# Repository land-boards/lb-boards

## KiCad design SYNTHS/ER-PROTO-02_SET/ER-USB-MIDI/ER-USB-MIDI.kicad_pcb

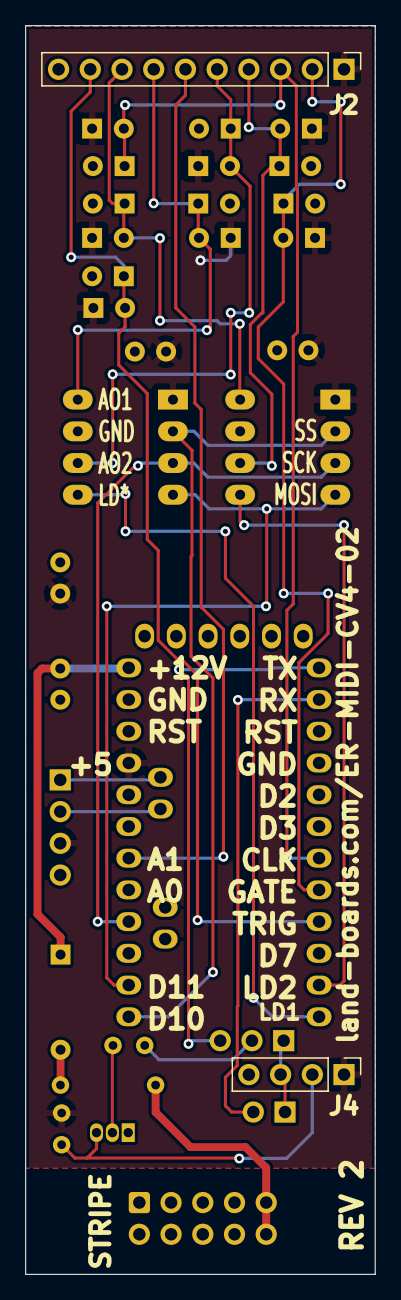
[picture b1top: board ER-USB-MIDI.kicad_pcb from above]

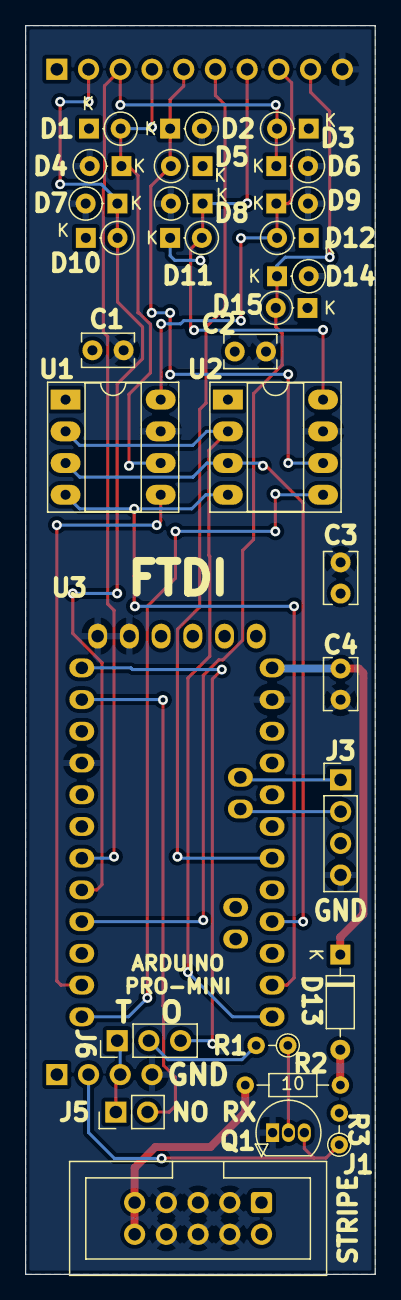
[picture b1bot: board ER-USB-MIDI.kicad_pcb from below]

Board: 2 copper layers, 28.0 x 100.0 mm, 32 parts (30 on the bottom side), 26 nets.

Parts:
C1, C2, C3, C4: 0.1uF; C_Rect_L4.0mm_W2.5mm_P2.50mm
D1, D2, D3, D4, D5, D6, D7, D8, D9, D10, D11, D12, D14, D15: BAT41; D_DO-35_SOD27_P2.54mm_Vertical_KathodeUp
D13: BAT41; D_DO-35_SOD27_P7.62mm_Horizontal
J1: CONN, IDC, 2X5; IDC-Header_2x05_P2.54mm_Vertical
J2: HEADER, STRT, 1x10; PinHeader_1x10_P2.54mm_Vertical
J3: Conn_01x04; PinHeader_1x04_P2.54mm_Vertical
J4: HEADER, STRT, 1x4; PinHeader_1x04_P2.54mm_Vertical
J5: HEADER, STRT, 1x2; PinHeader_1x02_P2.54mm_Vertical
J6: Conn_01x03; PinHeader_1x03_P2.54mm_Vertical
Q1: 2N3904; TO-92_Inline
R1: 2.2K; R_Axial_DIN0204_L3.6mm_D1.6mm_P2.54mm_Vertical
R2: 10; R_Axial_DIN0204_L3.6mm_D1.6mm_P7.62mm_Horizontal
R3: 470; R_Axial_DIN0204_L3.6mm_D1.6mm_P2.54mm_Vertical
U1, U2: MCP4822-E/P; DIP-8_W7.62mm_Socket_LongPads
U3: ARDUINO PRO MINI 5V; ArduProMini

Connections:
+5V: C1.1, C2.1, C3.1, D1.1 (K), D3.1 (K), D5.1 (K), D10.1 (K), D11.1 (K), D12.1 (K), D15.1 (K), J2.1, J3.3, J4.1, R3.2, U1.1 (Vdd), U2.1 (Vdd), U3.22 (Vcc2)
+12P: C4.1, D13.1 (K), U3.19 (RAW)
+12V: J1.9, J1.10, R2.1
/CLK_D: D3.2 (A), D6.1 (K), J2.3, U3.13 (D4)
/CV1_D: D8.1 (K), D11.2 (A), J2.7, U2.8 (VA)
/CV2_D: D2.1 (K), D5.2 (A), J2.5, U2.6 (VB)
/CV3_D: D9.1 (K), D12.2 (A), J2.8, U1.8 (VA)
/CV4_D: D1.2 (A), D4.1 (K), J2.4, U1.6 (VB)
/GATE_D: D7.1 (K), D10.2 (A), J2.2, U3.14 (D5)
/LDAC1*: U2.5 (~LDAC), U3.18 (D9)
/LDAC2*: U1.5 (~LDAC), U3.17 (D8)
/MIDI_IN: J4.3, J5.1, J6.1
/MIDI_OUT: J4.2, Q1.3 (C), R3.1
/MOSI: U1.4 (SDI), U2.4 (SDI), U3.29 (D11)
/POT: J2.6, U3.25 (A1)
/RBO: Q1.2 (B), R1.1
/SCK: U1.3 (SCK), U2.3 (SCK), U3.27 (D13)
/SCL: J3.1, U3.31 (A5/SCL)
/SDA: J3.2, U3.32 (A4/SDA)
/SS: U1.2 (~CS), U2.2 (~CS), U3.30 (D10)
/TRIG_D: D14.1 (K), D15.2 (A), J2.9, U3.15 (D6)
/TXD: J6.3, U3.7 (TX0)
GND: C1.2, C2.2, C3.2, C4.2, D2.2 (A), D4.2 (A), D6.2 (A), D7.2 (A), D8.2 (A), D9.2 (A), D14.2 (A), J1.3, J1.4, J1.5, J1.6, J1.7, J1.8, J2.10, J3.4, J4.4, Q1.1 (E), U1.7 (Vss), U2.7 (Vss), U3.1 (GND), U3.2 (GND2), U3.10 (GND), U3.20 (GND3)
unnamed: D13.2 (A), R2.2
unnamed: J5.2, U3.8 (RX1)
unnamed: J6.2, R1.2

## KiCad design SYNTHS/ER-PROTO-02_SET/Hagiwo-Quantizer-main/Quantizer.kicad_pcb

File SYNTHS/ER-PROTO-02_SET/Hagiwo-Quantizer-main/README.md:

# Hagiwo-Quantizer
A MCP4821 version of Hagiwo Quantizer

This is a version of Hagiwo Quantizer with a MCP4821 12 bit DAC. The code is still under review. Using the new DAC I have to check calibration.

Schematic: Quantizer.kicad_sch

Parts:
C1: 220p; C_Disc_D3.8mm_W2.6mm_P2.50mm
C2, C3: 10nf; C_Disc_D3.8mm_W2.6mm_P2.50mm
C4: 0.1uf; C_Disc_D3.8mm_W2.6mm_P2.50mm
C5: 10uf; CP_Radial_D6.3mm_P2.50mm
C6: 3.3uf; CP_Radial_D6.3mm_P2.50mm
C7: 100nf; C_Disc_D3.8mm_W2.6mm_P2.50mm
D1, D2, D3, D4, D5, D6, D8, D9: D; D_DO-34_SOD68_P7.62mm_Horizontal
D7: LED_ARBG; LED_D5.0mm-4_RGB_Wide_Pins
D10: 4841; D_DO-34_SOD68_P7.62mm_Horizontal
J1: CV; Jack_3.5mm_QingPu_WQP-PJ398SM_Vertical_CircularHoles
J2: SlideCV; Jack_3.5mm_QingPu_WQP-PJ398SM_Vertical_CircularHoles
J3: trigger; Jack_3.5mm_QingPu_WQP-PJ398SM_Vertical_CircularHoles
J4: AudioJack2_SwitchT; Jack_3.5mm_QingPu_WQP-PJ398SM_Vertical_CircularHoles
J5: Conn_02x05_Odd_Even; IDC-Header_2x05_P2.54mm_Vertical
R1, R2, R3, R6, R12: 470; R_Axial_DIN0207_L6.3mm_D2.5mm_P7.62mm_Horizontal
R4: 680K; R_Axial_DIN0207_L6.3mm_D2.5mm_P7.62mm_Horizontal
R5: 100k; R_Axial_DIN0207_L6.3mm_D2.5mm_P7.62mm_Horizontal
R7: 220; R_Axial_DIN0207_L6.3mm_D2.5mm_P7.62mm_Horizontal
R8, R9, R10: 330; R_Axial_DIN0207_L6.3mm_D2.5mm_P7.62mm_Horizontal
RV1: R_POT; Potentiometer_Alps_RK09K_Single_Vertical
SW1: Rotary_Encoder; RotaryEncoder_Alps_EC12E_Vertical_H20mm_CircularMountingHol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
SW2: SW_SPDT; PinHeader_1x03_P2.54mm_Vertical
U1: MCP4821; DIP-8_W7.62mm
U2: L7805; TO-220-3_Vertical
XA1: Arduino_Mini_02_Socket; Arduino_Mini_Socket

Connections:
+5V: C7.1, D1.1 (K), D3.1 (K), D5.1 (K), D8.1 (K), R7.1, RV1.1, U2.3 (OUT), XA1.VIN
+12V: D10.2 (A), J5.9, J5.10
CS: U1.2 (~CS), XA1.D10
CV: D1.2 (A), D2.1 (K), R2.1, R4.1, XA1.A0
GND: C1.2, C2.2, C3.2, C4.1, C5.2, C6.2, C7.2, D2.2 (A), D4.2 (A), D6.2 (A), D7.2 (A), D9.2 (A), J1.S, J2.S, J3.S, J4.S, J5.3, J5.4, J5.5, J5.6, J5.7, J5.8, R4.2, R5.2, RV1.3, SW1.C, SW2.2 (B), U1.5 (~LDAC), U1.7 (Vss), U2.2 (GND), XA1.GND2
Led1: R8.2, XA1.D3
Led2: R9.2, XA1.D5
Led3: R10.2, XA1.D4
unnamed: C4.2, R7.2, U1.1 (Vdd), U1.6 (~SHDN)
unnamed: C5.1, C6.1, D10.1 (K), U2.1 (IN)
unnamed: D5.2 (A), D6.1 (K), J3.T, R6.2
unnamed: D7.1 (RK), R8.1
unnamed: D7.3 (GK), R9.1
unnamed: D7.4 (BK), R10.1
unnamed: D8.2 (A), D9.1 (K), J4.T, R12.1
unnamed: J1.T, R2.2
unnamed: J2.T, R3.2
unnamed: J5.1, J5.2
unnamed: R1.2, RV1.2
unnamed: R12.2, U1.8 (Vout)
RotaryB: C2.1, SW1.B, XA1.D12
RotaryC: C3.1, SW1.A, XA1.D9
SCK: U1.3 (SCK), XA1.D13
SDI: U1.4 (SDI), XA1.D11
SW1: SW2.1 (A), XA1.D7
SW2: SW2.3 (C), XA1.D8
SlideCV: D3.2 (A), D4.1 (K), R3.1, R5.1, XA1.D6
SlidePot: C1.1, R1.1, XA1.A1
Trigger: R6.1, XA1.D2

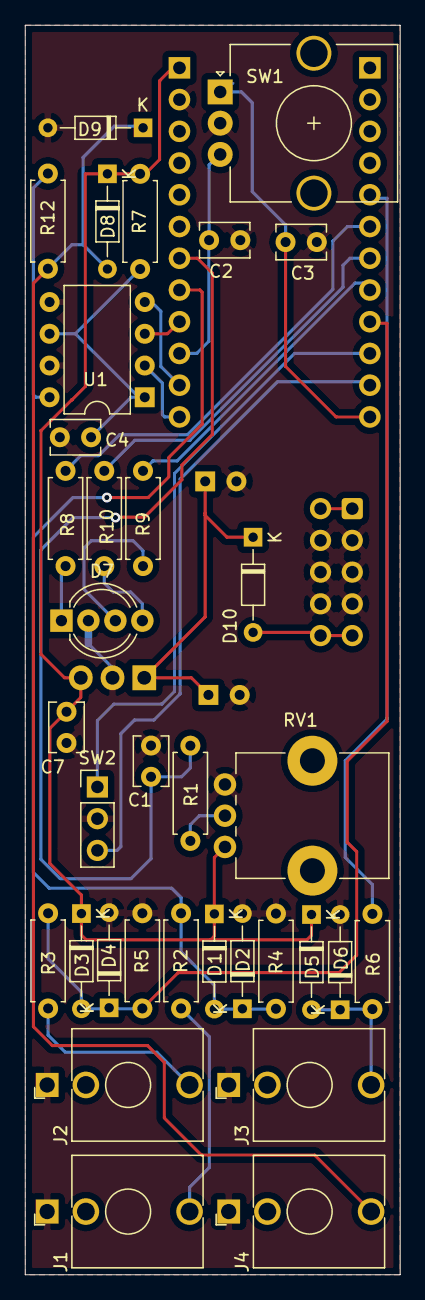
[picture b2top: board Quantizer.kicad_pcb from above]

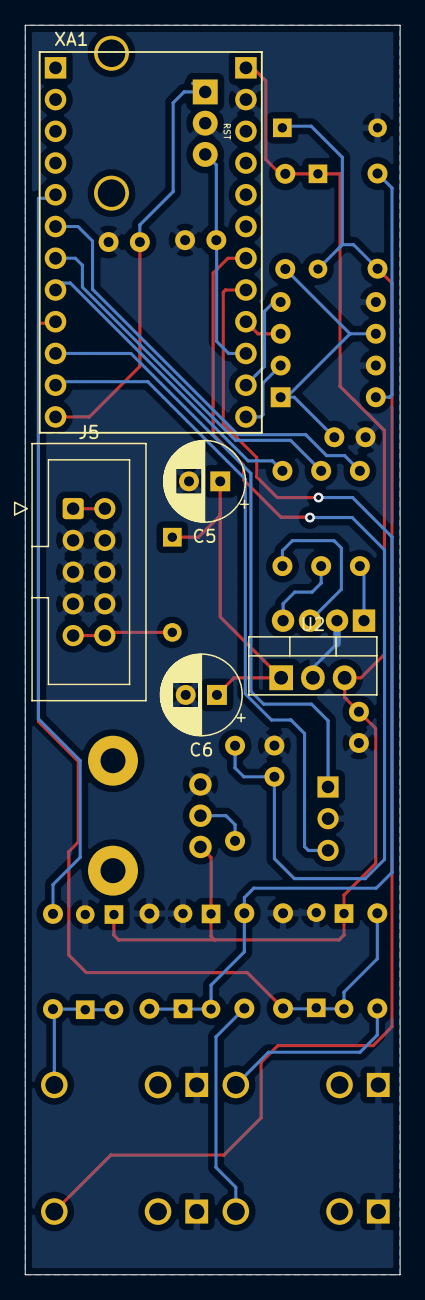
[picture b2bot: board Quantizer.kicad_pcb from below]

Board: 2 copper layers, 30.0 x 100.0 mm, 39 parts (5 on the bottom side), 29 nets.

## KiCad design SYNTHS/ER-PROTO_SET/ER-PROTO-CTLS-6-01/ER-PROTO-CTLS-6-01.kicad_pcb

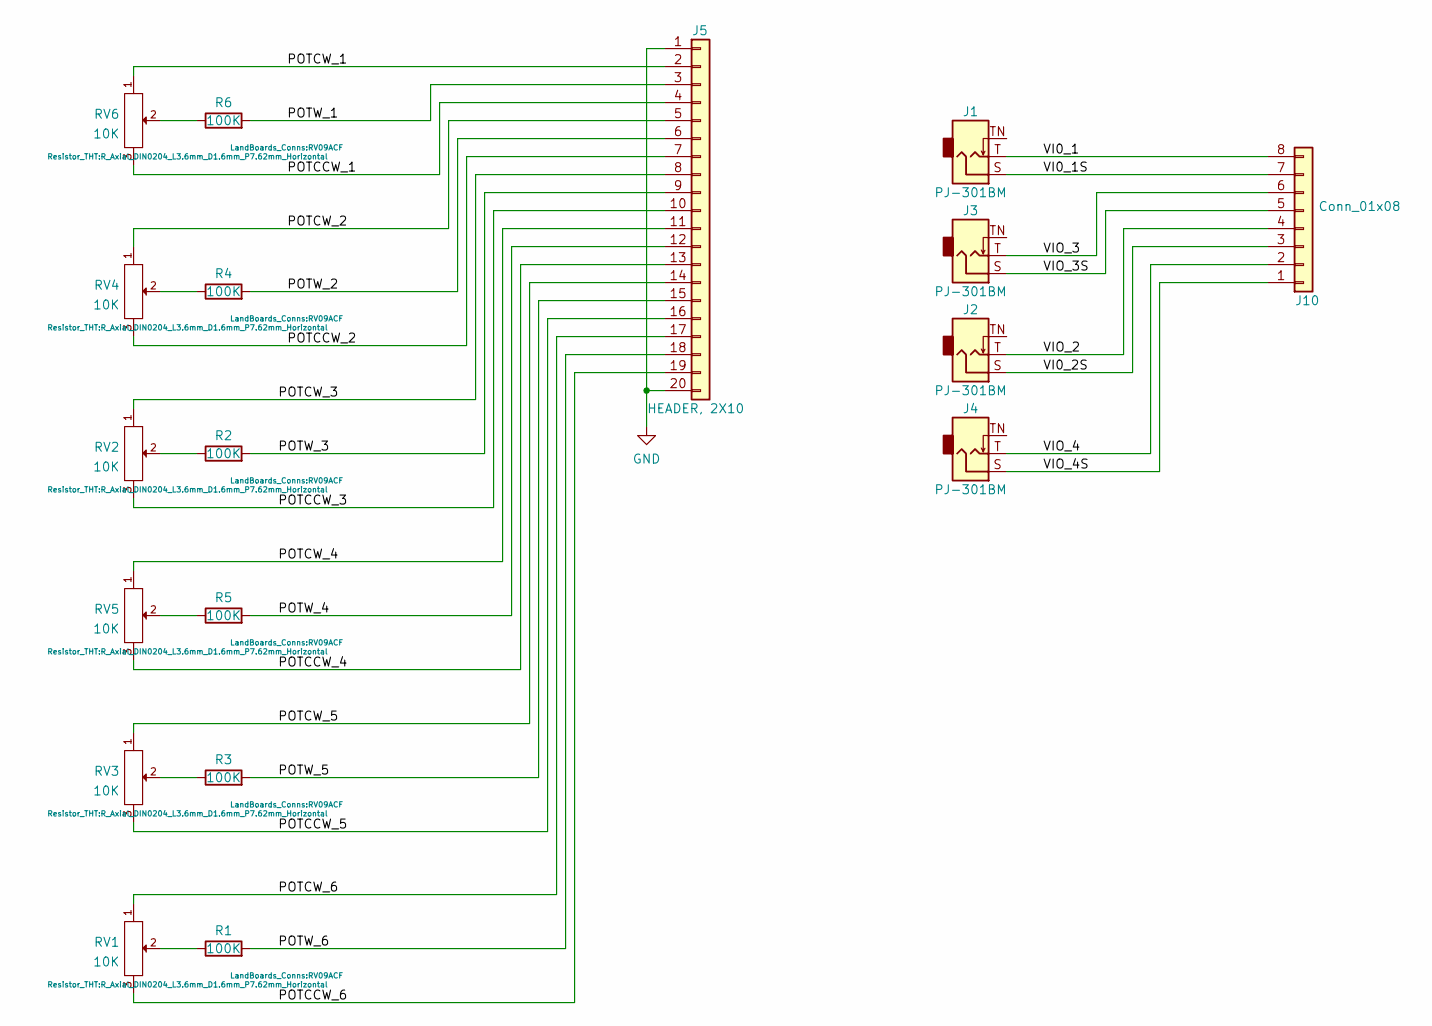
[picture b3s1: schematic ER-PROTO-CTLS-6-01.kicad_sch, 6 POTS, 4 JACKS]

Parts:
J1, J2, J3, J4: PJ-301BM; Jack_3.5mm_QingPu_WQP-PJ301BM_Vertical
J5: HEADER, 2X10; PinHeader_2x10_P2.54mm_Vertical
J10: Conn_01x08; PinHeader_1x08_P2.54mm_Vertical
R1, R2, R3, R4, R5, R6: 100K; R_Axial_DIN0204_L3.6mm_D1.6mm_P7.62mm_Horizontal
RV1, RV2, RV3, RV4, RV5, RV6: 10K; RV09ACF

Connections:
/POTCCW_1: J5.4, RV6.3
/POTCCW_2: J5.7, RV4.3
/POTCCW_3: J5.10, RV2.3
/POTCCW_4: J5.13, RV5.3
/POTCCW_5: J5.16, RV3.3
/POTCCW_6: J5.19, RV1.3
/POTCW_1: J5.2, RV6.1
/POTCW_2: J5.5, RV4.1
/POTCW_3: J5.8, RV2.1
/POTCW_4: J5.11, RV5.1
/POTCW_5: J5.14, RV3.1
/POTCW_6: J5.17, RV1.1
/POTW_1: J5.3, R6.2
/POTW_2: J5.6, R4.2
/POTW_3: J5.9, R2.2
/POTW_4: J5.12, R5.2
/POTW_5: J5.15, R3.2
/POTW_6: J5.18, R1.2
/VI0_1: J1.T, J10.8
/VI0_1S: J1.S, J10.7
/VI0_2S: J2.S, J10.3
/VIO_2: J2.T, J10.4
/VIO_3: J3.T, J10.6
/VIO_3S: J3.S, J10.5
/VIO_4: J4.T, J10.2
/VIO_4S: J4.S, J10.1
GND: J5.1, J5.20
unnamed: R1.1, RV1.2
unnamed: R2.1, RV2.2
unnamed: R3.1, RV3.2
unnamed: R4.1, RV4.2
unnamed: R5.1, RV5.2
unnamed: R6.1, RV6.2

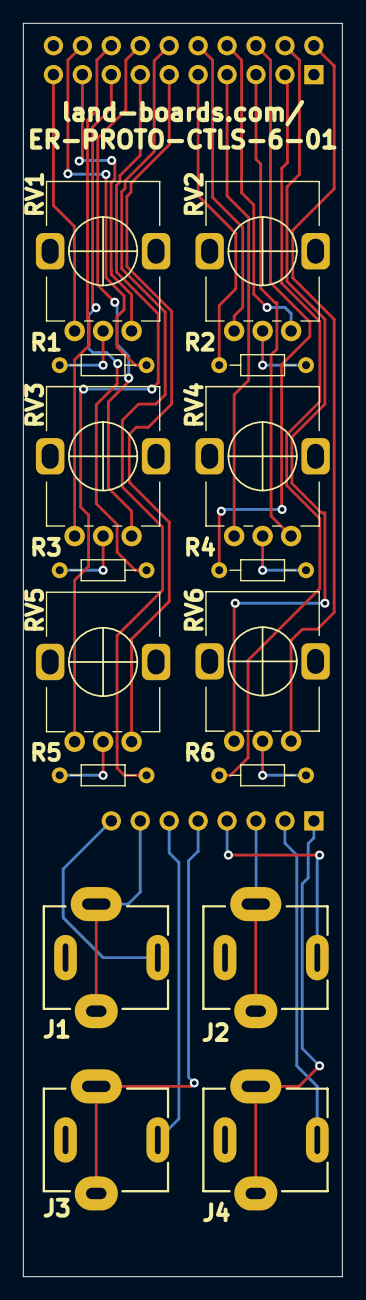
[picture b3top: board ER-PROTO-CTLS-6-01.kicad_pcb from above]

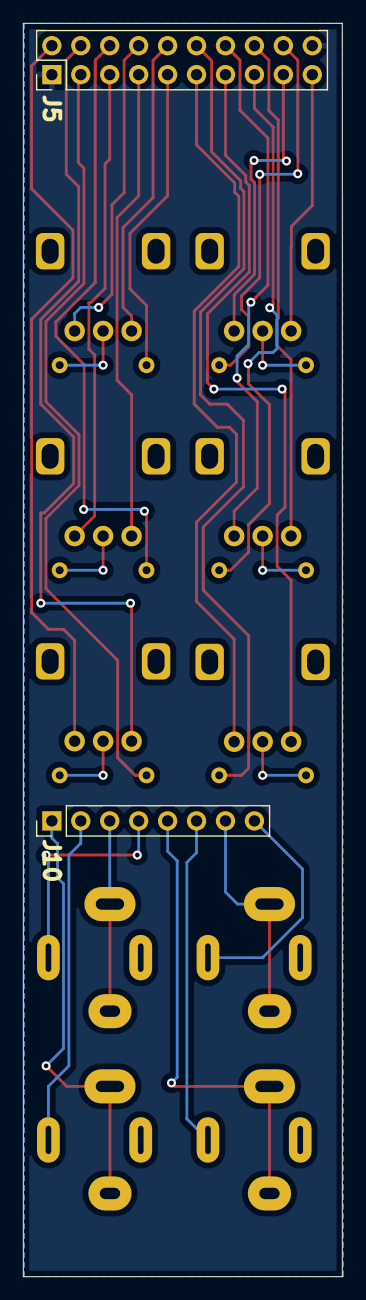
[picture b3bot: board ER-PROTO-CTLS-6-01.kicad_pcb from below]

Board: 2 copper layers, 28.0 x 110.0 mm, 18 parts (2 on the bottom side), 33 nets.

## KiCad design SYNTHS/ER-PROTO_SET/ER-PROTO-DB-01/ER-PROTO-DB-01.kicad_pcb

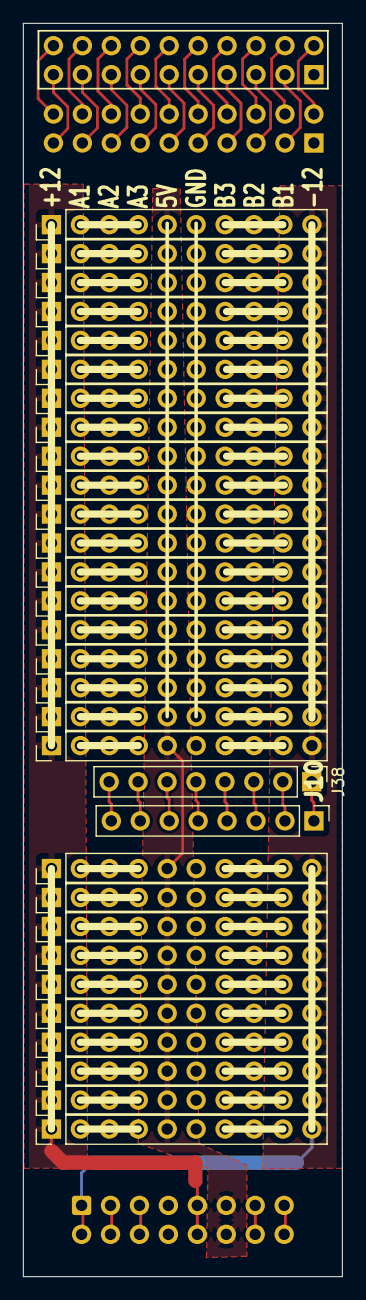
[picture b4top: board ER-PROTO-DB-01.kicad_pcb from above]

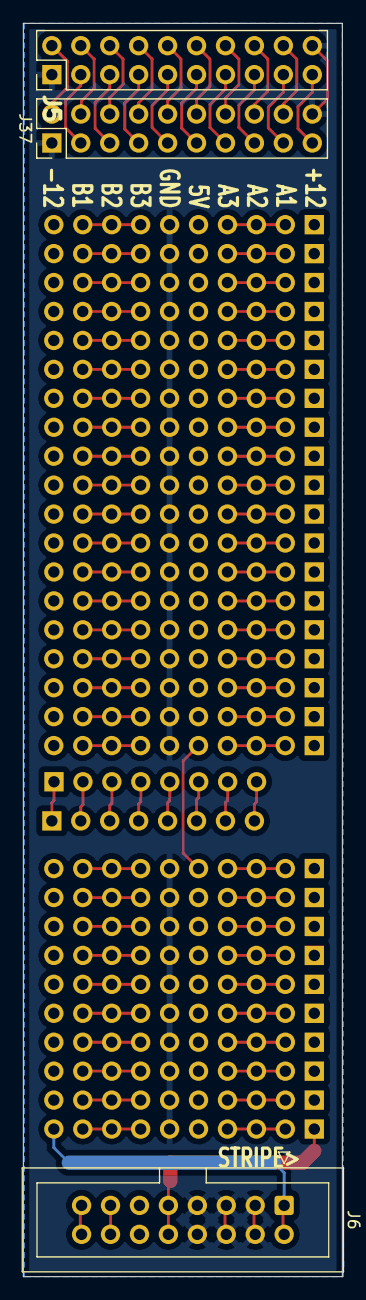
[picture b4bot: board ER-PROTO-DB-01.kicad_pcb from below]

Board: 2 copper layers, 28.0 x 110.0 mm, 34 parts (3 on the bottom side), 90 nets.

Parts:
J5, J37: HEADER, 2X10; PinHeader_2x10_P2.54mm_Vertical
J6: HEADER, 2X8; IDC-Header_2x08_P2.54mm_Vertical
J7, J8, J9, J11, J12, J13, J14, J15, J16, J17, J18, J19, J20, J21, J22, J23, J24, J25, J26, J27, J28, J29, J30, J31, J32, J33, J34, J35, J36: Conn_01x10; PinHeader_1x10_P2.54mm_Vertical
J10, J38: Conn_01x08; PinHeader_1x08_P2.54mm_Vertical

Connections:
+5V: J6.11, J6.12, J7.5, J8.5, J9.5, J11.5, J12.5, J13.5, J14.5, J15.5, J16.5, J17.5, J18.5, J19.5, J20.5, J21.5, J22.5, J23.5, J24.5, J25.5, J26.5, J27.5, J28.5, J29.5, J30.5, J31.5, J32.5, J33.5, J34.5, J35.5, J36.5
+12V: J6.9, J6.10, J7.1, J8.1, J9.1, J11.1, J12.1, J13.1, J14.1, J15.1, J16.1, J17.1, J18.1, J19.1, J20.1, J21.1, J22.1, J23.1, J24.1, J25.1, J26.1, J27.1, J28.1, J29.1, J30.1, J31.1, J32.1, J33.1, J34.1, J35.1, J36.1
-12V: J6.1, J6.2, J7.10, J8.10, J9.10, J11.10, J12.10, J13.10, J14.10, J15.10, J16.10, J17.10, J18.10, J19.10, J20.10, J21.10, J22.10, J23.10, J24.10, J25.10, J26.10, J27.10, J28.10, J29.10, J30.10, J31.10, J32.10, J33.10, J34.10, J35.10, J36.10
/CV: J6.13, J6.14
/GATE: J6.15, J6.16
/POTCCW_1: J5.4, J37.4
/POTCCW_2: J5.7, J37.7
/POTCCW_3: J5.10, J37.10
/POTCCW_4: J5.13, J37.13
/POTCCW_5: J5.16, J37.16
/POTCCW_6: J5.19, J37.19
/POTCW_1: J5.2, J37.2
/POTCW_2: J5.5, J37.5
/POTCW_3: J5.8, J37.8
/POTCW_4: J5.11, J37.11
/POTCW_5: J5.14, J37.14
/POTCW_6: J5.17, J37.17
/POTW_1: J5.3, J37.3
/POTW_2: J5.6, J37.6
/POTW_3: J5.9, J37.9
/POTW_4: J5.12, J37.12
/POTW_5: J5.15, J37.15
/POTW_6: J5.18, J37.18
/VI0_1: J10.8, J38.8
/VI0_1S: J10.7, J38.7
/VI0_2S: J10.3, J38.3
/VIO_2: J10.4, J38.4
/VIO_3: J10.6, J38.6
/VIO_3S: J10.5, J38.5
/VIO_4: J10.2, J38.2
/VIO_4S: J10.1, J38.1
GND: J5.1, J5.20, J6.3, J6.4, J6.5, J6.6, J6.7, J6.8, J7.6, J8.6, J9.6, J11.6, J12.6, J13.6, J14.6, J15.6, J16.6, J17.6, J18.6, J19.6, J20.6, J21.6, J22.6, J23.6, J24.6, J25.6, J26.6, J27.6, J28.6, J29.6, J30.6, J31.6, J32.6, J33.6, J34.6, J35.6, J36.6, J37.1, J37.20
unnamed: J7.2, J7.3, J7.4
unnamed: J7.7, J7.8, J7.9
unnamed: J8.2, J8.3, J8.4
unnamed: J8.7, J8.8, J8.9
unnamed: J9.2, J9.3, J9.4
unnamed: J9.7, J9.8, J9.9
unnamed: J11.2, J11.3, J11.4
unnamed: J11.7, J11.8, J11.9
unnamed: J12.2, J12.3, J12.4
unnamed: J12.7, J12.8, J12.9
unnamed: J13.2, J13.3, J13.4
unnamed: J13.7, J13.8, J13.9
unnamed: J14.2, J14.3, J14.4
unnamed: J14.7, J14.8, J14.9
unnamed: J15.2, J15.3, J15.4
unnamed: J15.7, J15.8, J15.9
unnamed: J16.2, J16.3, J16.4
unnamed: J16.7, J16.8, J16.9
unnamed: J17.2, J17.3, J17.4
unnamed: J17.7, J17.8, J17.9
unnamed: J18.2, J18.3, J18.4
unnamed: J18.7, J18.8, J18.9
unnamed: J19.2, J19.3, J19.4
unnamed: J19.7, J19.8, J19.9
unnamed: J20.2, J20.3, J20.4
unnamed: J20.7, J20.8, J20.9
unnamed: J21.2, J21.3, J21.4
unnamed: J21.7, J21.8, J21.9
unnamed: J22.2, J22.3, J22.4
unnamed: J22.7, J22.8, J22.9
unnamed: J23.2, J23.3, J23.4
unnamed: J23.7, J23.8, J23.9
unnamed: J24.2, J24.3, J24.4
unnamed: J24.7, J24.8, J24.9
unnamed: J25.2, J25.3, J25.4
unnamed: J25.7, J25.8, J25.9
unnamed: J26.2, J26.3, J26.4
unnamed: J26.7, J26.8, J26.9
unnamed: J27.2, J27.3, J27.4
unnamed: J27.7, J27.8, J27.9
unnamed: J28.2, J28.3, J28.4
unnamed: J28.7, J28.8, J28.9
unnamed: J29.2, J29.3, J29.4
unnamed: J29.7, J29.8, J29.9
unnamed: J30.2, J30.3, J30.4
unnamed: J30.7, J30.8, J30.9
unnamed: J31.2, J31.3, J31.4
unnamed: J31.7, J31.8, J31.9
unnamed: J32.2, J32.3, J32.4
unnamed: J32.7, J32.8, J32.9
unnamed: J33.2, J33.3, J33.4
unnamed: J33.7, J33.8, J33.9
unnamed: J34.2, J34.3, J34.4
unnamed: J34.7, J34.8, J34.9
unnamed: J35.2, J35.3, J35.4
unnamed: J35.7, J35.8, J35.9
unnamed: J36.2, J36.3, J36.4
unnamed: J36.7, J36.8, J36.9

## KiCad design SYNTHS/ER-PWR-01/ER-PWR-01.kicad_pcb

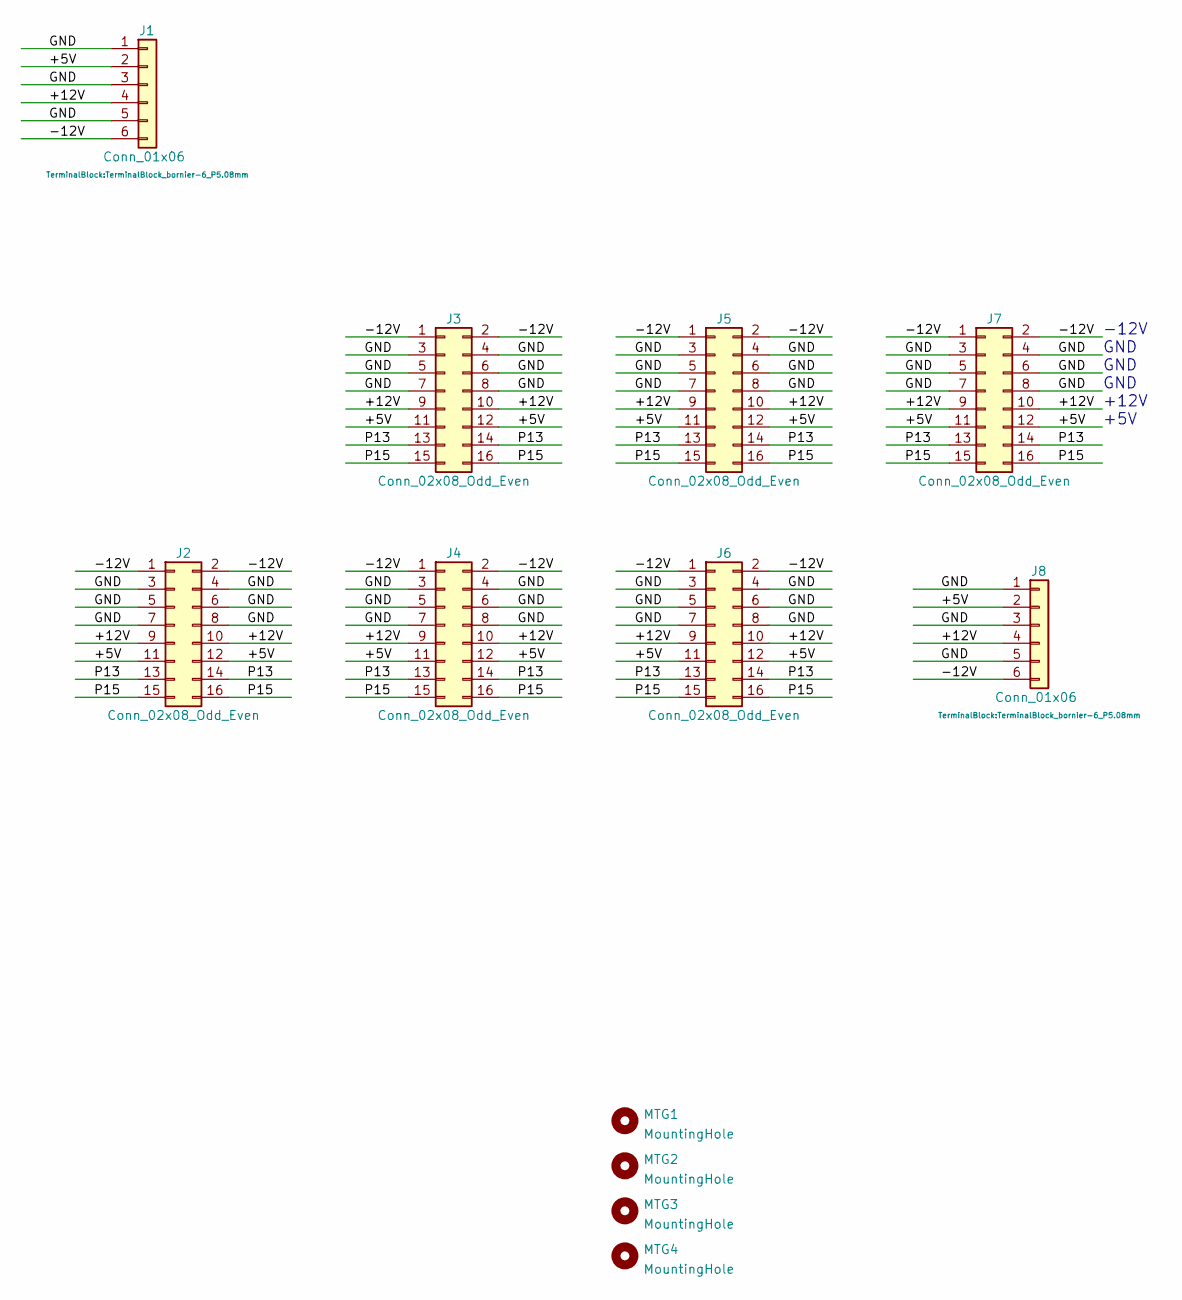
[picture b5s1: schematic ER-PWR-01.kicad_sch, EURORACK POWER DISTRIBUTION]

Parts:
J1, J8: Conn_01x06; TerminalBlock_bornier-6_P5.08mm
J2, J3, J4, J5, J6, J7: Conn_02x08_Odd_Even; IDC-Header_2x08_P2.54mm_Vertical
MTG1, MTG2, MTG3, MTG4: MountingHole; MTG-4-40

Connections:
/+5V: J1.2, J2.11, J2.12, J3.11, J3.12, J4.11, J4.12, J5.11, J5.12, J6.11, J6.12, J7.11, J7.12, J8.2
/+12V: J1.4, J2.9, J2.10, J3.9, J3.10, J4.9, J4.10, J5.9, J5.10, J6.9, J6.10, J7.9, J7.10, J8.4
/-12V: J1.6, J2.1, J2.2, J3.1, J3.2, J4.1, J4.2, J5.1, J5.2, J6.1, J6.2, J7.1, J7.2, J8.6
/GND: J1.1, J1.3, J1.5, J2.3, J2.4, J2.5, J2.6, J2.7, J2.8, J3.3, J3.4, J3.5, J3.6, J3.7, J3.8, J4.3, J4.4, J4.5, J4.6, J4.7, J4.8, J5.3, J5.4, J5.5, J5.6, J5.7, J5.8, J6.3, J6.4, J6.5, J6.6, J6.7, J6.8, J7.3, J7.4, J7.5, J7.6, J7.7, J7.8, J8.1, J8.3, J8.5
/P13: J2.13, J2.14, J3.13, J3.14, J4.13, J4.14, J5.13, J5.14, J6.13, J6.14, J7.13, J7.14
/P15: J2.15, J2.16, J3.15, J3.16, J4.15, J4.16, J5.15, J5.16, J6.15, J6.16, J7.15, J7.16

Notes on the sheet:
-12V GND GND GND +12V +5V

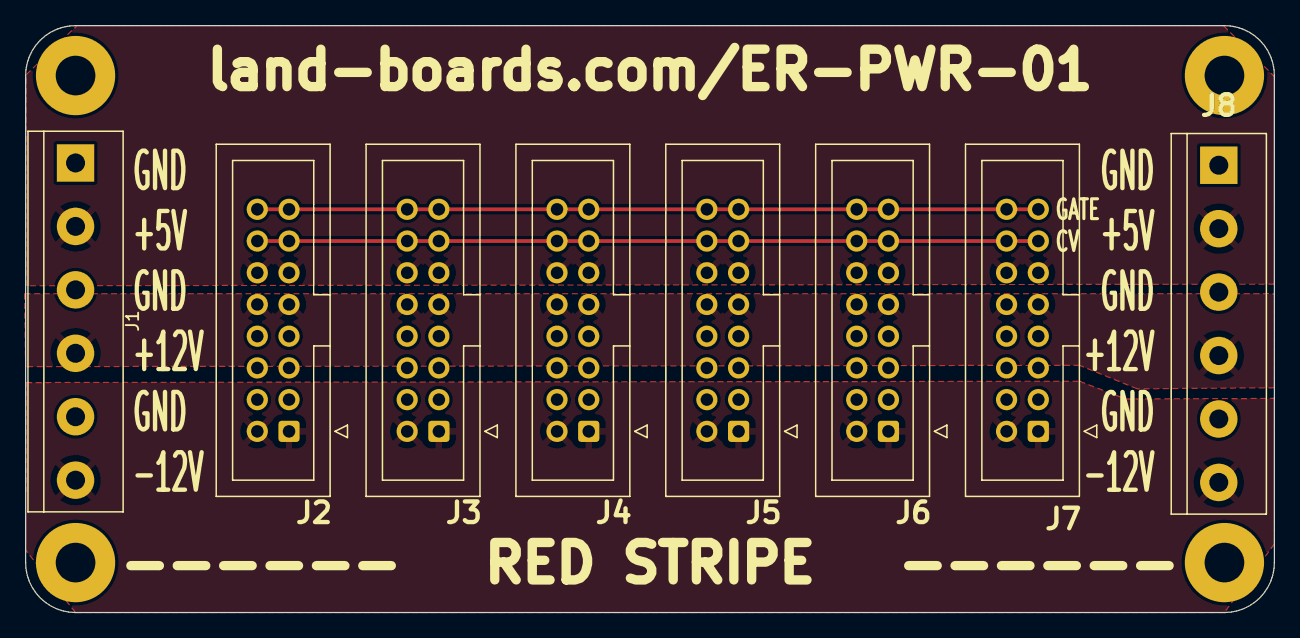
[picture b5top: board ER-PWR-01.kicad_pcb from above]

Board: 2 copper layers, 100.0 x 47.0 mm, 12 parts (0 on the bottom side), 6 nets.

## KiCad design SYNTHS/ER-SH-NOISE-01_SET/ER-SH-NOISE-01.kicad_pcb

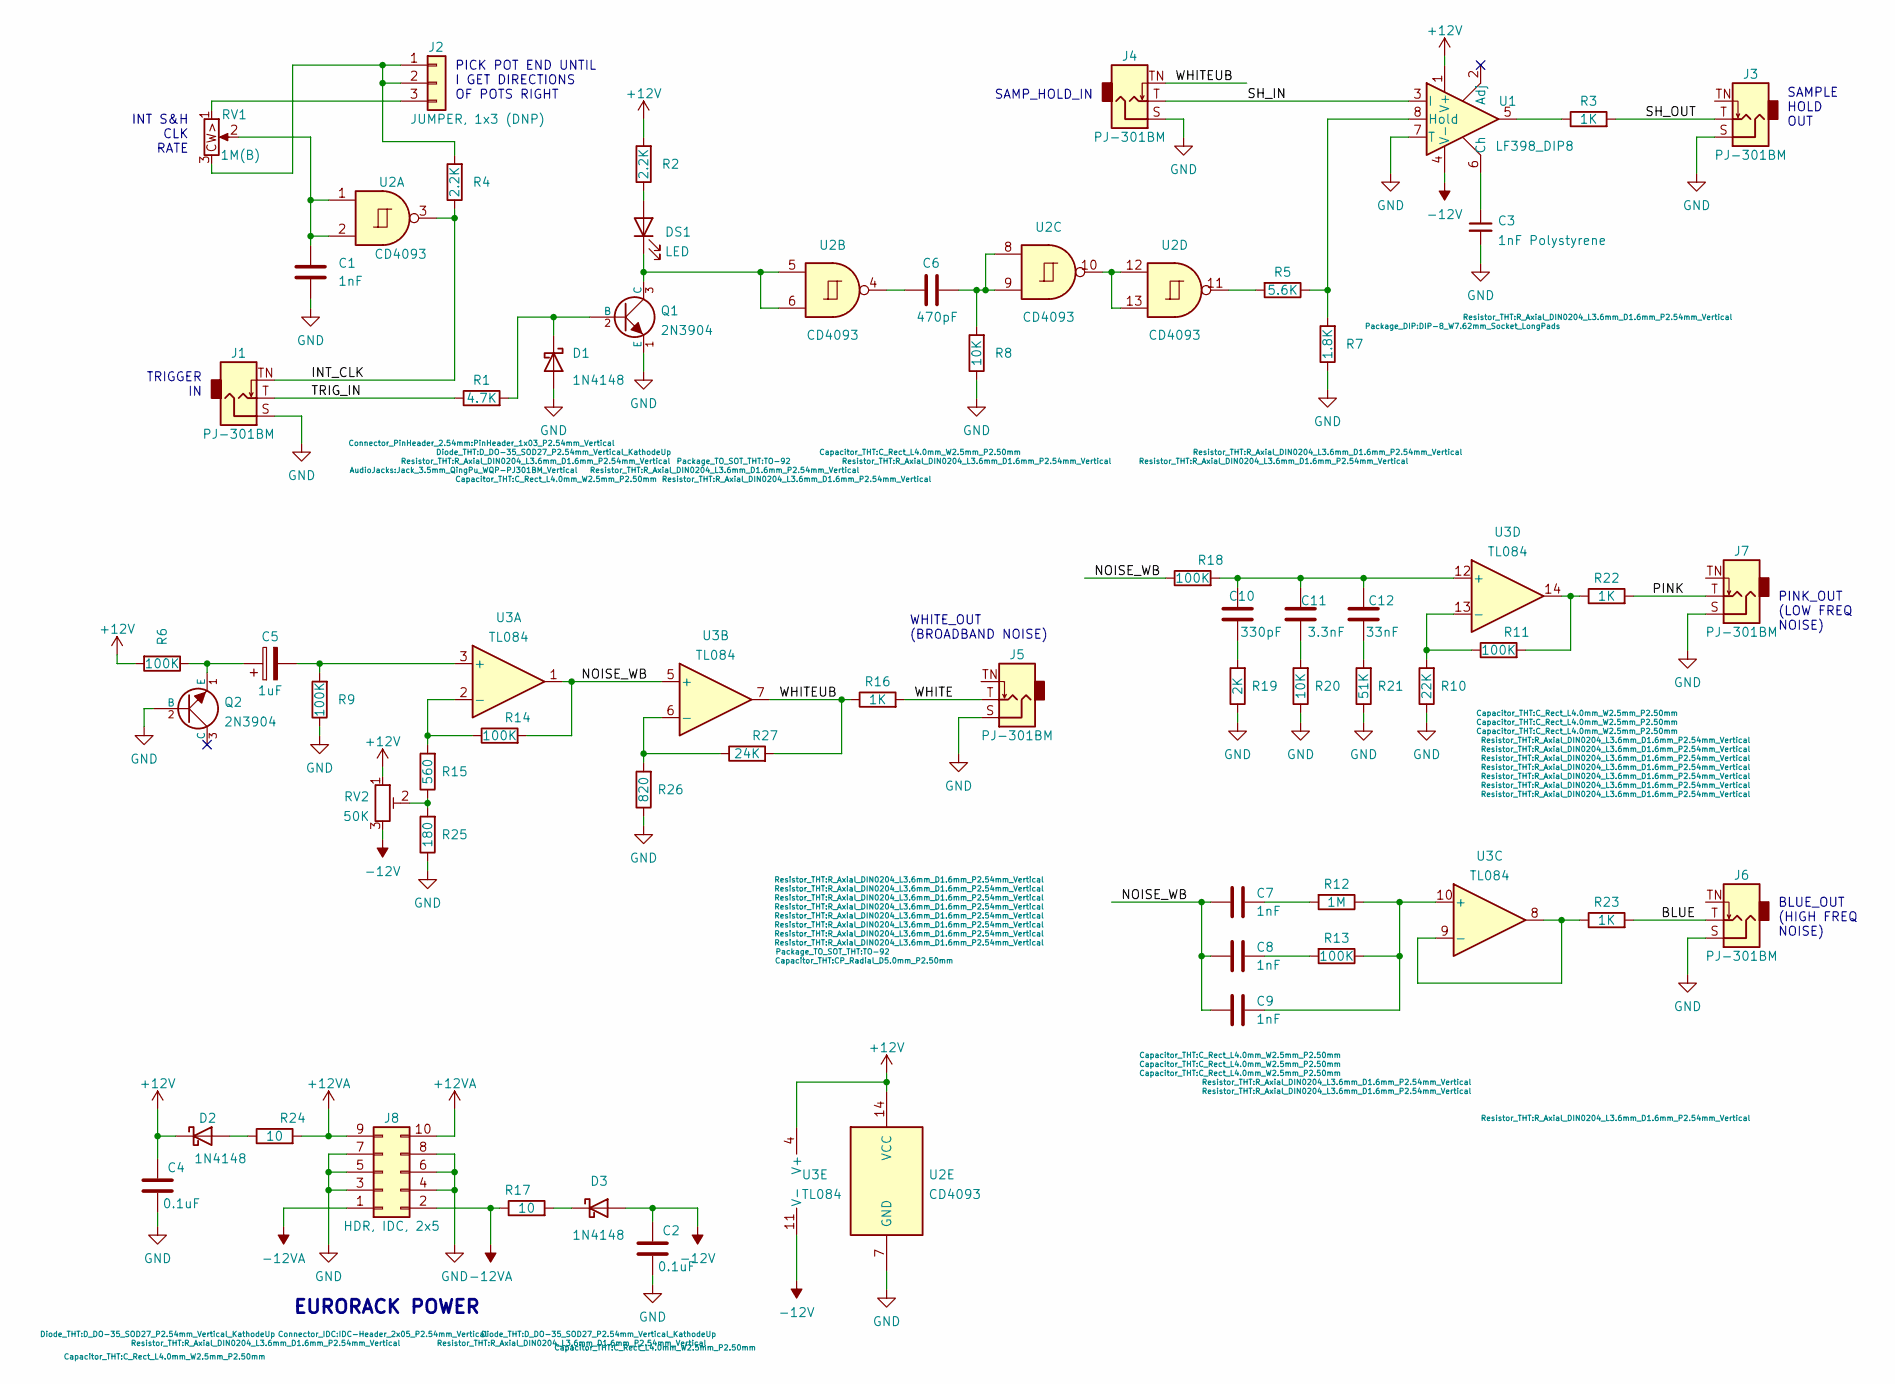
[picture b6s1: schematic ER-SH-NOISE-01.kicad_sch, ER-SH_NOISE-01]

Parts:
C1, C7, C8, C9: 1nF; C_Rect_L4.0mm_W2.5mm_P2.50mm
C2, C4: 0.1uF; C_Rect_L4.0mm_W2.5mm_P2.50mm
C3: 1nF Polystyrene; C_Radial_D5.0mm_H7.0mm_P2.00mm
C5: 1uF; CP_Radial_D5.0mm_P2.50mm
C6: 470pF; C_Rect_L4.0mm_W2.5mm_P2.50mm
C10: 330pF; C_Rect_L4.0mm_W2.5mm_P2.50mm
C11: 3.3nF; C_Rect_L4.0mm_W2.5mm_P2.50mm
C12: 33nF; C_Rect_L4.0mm_W2.5mm_P2.50mm
D1, D2, D3: 1N4148; D_DO-35_SOD27_P2.54mm_Vertical_KathodeUp
DS1: LED; LED_D5.0mm
J1, J3, J4, J5, J6, J7: PJ-301BM; Jack_3.5mm_QingPu_WQP-PJ301BM_Vertical
J2: JUMPER, 1x3 (DNP); PinHeader_1x03_P2.54mm_Vertical
J8: HDR, IDC, 2x5; IDC-Header_2x05_P2.54mm_Vertical
Q1, Q2: 2N3904; TO-92
R1: 4.7K; R_Axial_DIN0204_L3.6mm_D1.6mm_P2.54mm_Vertical
R2, R4: 2.2K; R_Axial_DIN0204_L3.6mm_D1.6mm_P2.54mm_Vertical
R3, R16, R22, R23: 1K; R_Axial_DIN0204_L3.6mm_D1.6mm_P2.54mm_Vertical
R5: 5.6K; R_Axial_DIN0204_L3.6mm_D1.6mm_P2.54mm_Vertical
R6, R9, R11, R13, R14, R18: 100K; R_Axial_DIN0204_L3.6mm_D1.6mm_P2.54mm_Vertical
R7: 1.8K; R_Axial_DIN0204_L3.6mm_D1.6mm_P2.54mm_Vertical
R8, R20: 10K; R_Axial_DIN0204_L3.6mm_D1.6mm_P2.54mm_Vertical
R10: 22K; R_Axial_DIN0204_L3.6mm_D1.6mm_P2.54mm_Vertical
R12: 1M; R_Axial_DIN0204_L3.6mm_D1.6mm_P2.54mm_Vertical
R15: 560; R_Axial_DIN0204_L3.6mm_D1.6mm_P2.54mm_Vertical
R17, R24: 10; R_Axial_DIN0204_L3.6mm_D1.6mm_P2.54mm_Vertical
R19: 2K; R_Axial_DIN0204_L3.6mm_D1.6mm_P2.54mm_Vertical
R21: 51K; R_Axial_DIN0204_L3.6mm_D1.6mm_P2.54mm_Vertical
R25: 180; R_Axial_DIN0204_L3.6mm_D1.6mm_P2.54mm_Vertical
R26: 820; R_Axial_DIN0204_L3.6mm_D1.6mm_P2.54mm_Vertical
R27: 24K; R_Axial_DIN0204_L3.6mm_D1.6mm_P2.54mm_Vertical
RV1: 1M(B); RV09ACF
RV2: 50K; Potentiometer_Bourns_3299W_Vertical
U1: LF398_DIP8; DIP-8_W7.62mm_Socket_LongPads
U2: CD4093; DIP-14_W7.62mm_Socket_LongPads
U3: TL084; DIP-14_W7.62mm_Socket_LongPads

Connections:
+12V: C4.1, D2.1 (K), R2.2, R6.2, RV2.1, U1.1 (V+), U2.14 (VCC), U3.4 (V+)
+12VA: J8.9, J8.10, R24.2
-12V: C2.1, D3.2 (A), RV2.3, U1.4 (V-), U3.11 (V-)
-12VA: J8.1, J8.2, R17.1
/BLUE: J6.T, R23.2
/INT_CLK: J1.TN, R4.1, U2.3
/NOISE_WB: C7.2, C8.2, C9.2, R14.2, R18.1, U3.1, U3.5 (+)
/PINK: J7.T, R22.2
/SH_IN: J4.T, U1.3 (I)
/SH_OUT: J3.T, R3.2
/TRIG_IN: J1.T, R1.1
/WHITE: J5.T, R16.2
/WHITEUB: J4.TN, R16.1, R27.2, U3.7
GND: C1.2, C2.2, C3.2, C4.2, D1.2 (A), J1.S, J3.S, J4.S, J5.S, J6.S, J7.S, J8.3, J8.4, J8.5, J8.6, J8.7, J8.8, Q1.1 (E), Q2.2 (B), R7.1, R8.1, R9.1, R10.1, R19.1, R20.1, R21.1, R25.1, R26.1, U1.7 (T), U2.7 (GND)
unnamed: C1.1, RV1.2, U2.1, U2.2
unnamed: C3.1, U1.6 (Ch)
unnamed: C5.1, Q2.1 (E), R6.1
unnamed: C5.2, R9.2, U3.3 (+)
unnamed: C6.1, U2.4
unnamed: C6.2, R8.2, U2.8, U2.9
unnamed: C7.1, R12.2
unnamed: C8.1, R13.2
unnamed: C9.1, R12.1, R13.1, U3.10 (+)
unnamed: C10.1, R19.2
unnamed: C10.2, C11.2, C12.2, R18.2, U3.12 (+)
unnamed: C11.1, R20.2
unnamed: C12.1, R21.2
unnamed: D1.1 (K), Q1.2 (B), R1.2
unnamed: D2.2 (A), R24.1
unnamed: D3.1 (K), R17.2
unnamed: DS1.1 (K), Q1.3 (C), U2.5, U2.6
unnamed: DS1.2 (A), R2.1
unnamed: J2.1, J2.2, R4.2, RV1.3
unnamed: J2.3, RV1.1
unnamed: R3.1, U1.5
unnamed: R5.1, R7.2, U1.8 (Hold)
unnamed: R5.2, U2.11
unnamed: R10.2, R11.1, U3.13 (-)
unnamed: R11.2, R22.1, U3.14
unnamed: R14.1, R15.2, U3.2 (-)
unnamed: R15.1, R25.2, RV2.2
unnamed: R23.1, U3.8, U3.9 (-)
unnamed: U2.10, U2.12, U2.13
unnamed: R26.2, R27.1, U3.6 (-)

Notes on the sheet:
EURORACK POWER
INT S&H CLK RATE
PICK POT END UNTIL I GET DIRECTIONS OF POTS RIGHT
SAMPLE HOLD OUT
BLUE_OUT (HIGH FREQ NOISE)
TRIGGER IN
PINK_OUT (LOW FREQ NOISE)
SAMP_HOLD_IN
WHITE_OUT (BROADBAND NOISE)

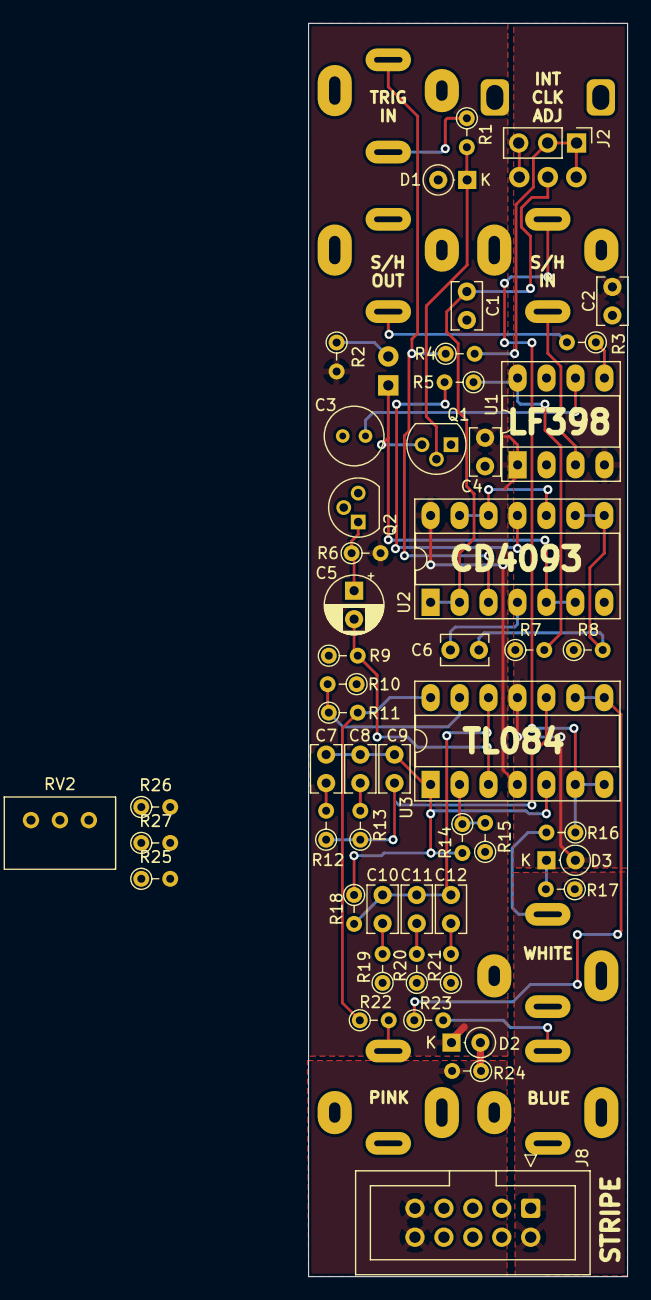
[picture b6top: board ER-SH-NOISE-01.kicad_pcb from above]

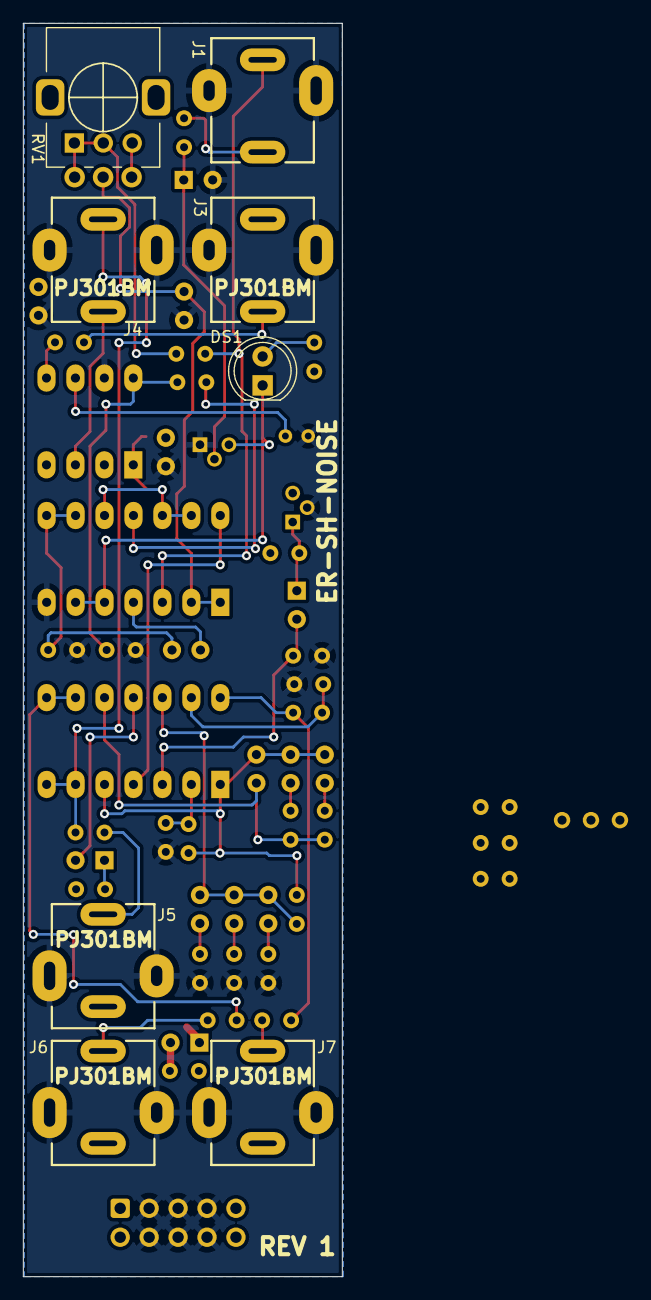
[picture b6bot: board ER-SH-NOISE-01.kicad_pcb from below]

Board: 2 copper layers, 28.0 x 110.0 mm, 58 parts (8 on the bottom side), 44 nets.
